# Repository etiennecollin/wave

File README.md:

# Wave <!-- omit from toc -->

 <sub>Wave v0.0.1 + MBK Blank Keycaps</sub>

<span>

</span>

---

- [What Is It](#what-is-it)
- [Features](#features)
- [Components List](#components-list)
  - [Keyboard](#keyboard)
  - [Plates Kit](#plates-kit)
- [Ordering the PCBs](#ordering-the-pcbs)
  - [Keyboard](#keyboard-1)
  - [Plates kit](#plates-kit-1)
    - [Switch Plates](#switch-plates)
    - [Back Plates](#back-plates)
- [QMK Firmware](#qmk-firmware)

## What Is It

The Wave is a small, minimalist, reversible keyboard inspired by the [Ferris](https://github.com/pierrechevalier83/ferris), the [Ferris Sweep](https://github.com/davidphilipbarr/Sweep), the [Swoop](https://github.com/jimmerricks/swoop), the [Sweep36](https://github.com/sadekbaroudi/sweep36), the [Piantor](https://github.com/beekeeb/piantor) and the [Chocofi](https://github.com/pashutk/chocofi) (thank you to the amazing creators of these keyboards). It aims to put together everything I like about these other models and to solve a few issues I found with them.

## Features

- Choc V1 switches
  - The switches can be soldered, or hot swapped using either Mill-Max or Kailh hot swap sockets
- Choc spacing (supports MBK keycaps)
- The same column stagger you loved on the [Ferris Sweep](https://github.com/davidphilipbarr/Sweep)
- 1.5u thumb key support
- Diode-less build
- Reversible PCB
- USB-C
- Mini DIN 4 (S-Video) connector used to connect both halves of the keyboard
  - The issue with TRRS connectors is that [they are not hot swap](https://docs.qmk.fm/#/feature_split_keyboard?id=considerations); disconnecting the cable while the keyboard is powered via usb risks damaging/breaking the controller by shorting the VCC pin to a GND or data pin.
  - The Mini DIN 4 connector solves this issue and is readily available on the market, being the cable used for S-Video.
- Switch plate and back plate available
- No LEDs

## Components List

### Keyboard

Here are the **required** components to build the Wave:

- 2x Keyboard PCBs (PCB manufacturers usually sell them in multiples of 5)
- 2x Elite-C V4 controllers
- 36x Choc V1 switches
- 36x MBK compatible keycaps
- 2x Mini DIN 4 Jack ([MDJ-004-FS](https://www.digikey.ca/en/products/detail/adam-tech/MDJ-004-FS/9832525))
- 1x Mini DIN 4 (S-Video) cable
- 1x USB-C Cable to connect to computer

Here are the **optional** components to build the Wave:

- Hot swap sockets, either:
  - 36x Kailh hot swap sockets for Choc switches
  - 72x Mill-Max hot swap sockets (preferably [3305](https://www.digikey.ca/en/products/detail/mill-max-manufacturing-corp/3305-1-15-15-47-27-10-0/13901953) or [7305](https://www.digikey.ca/en/products/detail/mill-max-manufacturing-corp/7305-0-15-15-47-27-10-0/1765737) sockets as they have a thinner profile)
- 2x reset switches ([B3U-1000P-B](https://www.digikey.ca/en/products/detail/omron-electronics-inc-emc-div/B3U-1000P-B/1811777))
  - The B3U-1000PM, B3U-1000P-B and B3U-1000PM-B variants will work as they have the same footprint.
- 10x Rubber feet/bumpers (I like these [RBS-12BK](https://www.digikey.ca/en/products/detail/essentra-components/RBS-12BK/3814603))

### Plates Kit

- 2x Switch plate PCBs (PCB manufacturers usually sell them in multiples of 5)
  - The switch plates may be used without back plates.
- 2x Back plate PCBs (PCB manufacturers usually sell them in multiples of 5)
  - The back plates **require** switch plates to screw into.
- 5x M2 6mm spacer ([970060244](https://www.digikey.ca/en/products/detail/w%C3%BCrth-elektronik/970060244/9488532))
- 10x M2 3mm screws ([I like these torx screws](https://www.ebay.ca/itm/154354213469?var=454428568064))

## Ordering the PCBs

### Keyboard

<sub>Wave PCB</sub>

To order the keyboard PCB, the following settings are recommended[^1]:

| Detail                  | Value                     |
| ----------------------- | ------------------------- |
| Gerber file             | `Wave_0.0.1.zip`          |
| Base material           | FR-4                      |
| Layers                  | 2                         |
| Different design        | 1                         |
| Delivery format         | Single PCB                |
| PCB thickness           | **1.6mm**                 |
| PCB color               | (Personal preference)     |
| Silkscreen              | (Personal preference)     |
| Surface finish          | (Personal preference)[^2] |
| Outer copper weight     | 1oz                       |
| Via Covering            | Tented                    |
| Board Outline Tolerance | ±0.2mm(Regular)           |
| Confirm production file | No                        |
| Remove order number     | Yes                       |
| Gold Fingers            | No                        |
| Castellated holes       | No                        |

### Plates kit

You will need to order two different PCBs; the switch plate one and the back plate one.

#### Switch Plates

<sub>Wave Switch Plate PCB</sub>

 <sub>Wave v0.0.1 Switch Plate</sub>

To order the switch plate PCB, the following settings are recommended[^1]:

| Detail                  | Value                         |
| ----------------------- | ----------------------------- |
| Gerber file             | `Wave_Switch_Plate_0.0.1.zip` |
| Base material           | FR-4                          |
| Different design        | 1                             |
| Layers                  | 2                             |
| Delivery format         | Single PCB                    |
| PCB thickness           | **1.2mm**                     |
| PCB color               | (Personal preference)         |
| Silkscreen              | (Personal preference)         |
| Surface finish          | (Personal preference)[^2]     |
| Outer copper weight     | 1oz                           |
| Via Covering            | Tented                        |
| Board Outline Tolerance | ±0.2mm(Regular)               |
| Confirm production file | No                            |
| Remove order number     | Yes                           |
| Gold Fingers            | No                            |
| Castellated holes       | No                            |

#### Back Plates

<sub>Wave Back Plate PCB</sub>

 <sub>Wave v0.0.1 Back Plate</sub>

To order the back plate PCB, the following settings are recommended[^1]:

| Detail                  | Value                       |
| ----------------------- | --------------------------- |
| Gerber file             | `Wave_Back_Plate_0.0.1.zip` |
| Base material           | FR-4                        |
| Different design        | 1                           |
| Layers                  | 2                           |
| Delivery format         | Single PCB                  |
| PCB thickness           | **1.6mm**                   |
| PCB color               | (Personal preference)       |
| Silkscreen              | (Personal preference)       |
| Surface finish          | (Personal preference)[^2]   |
| Outer copper weight     | 1oz                         |
| Via Covering            | Tented                      |
| Board Outline Tolerance | ±0.2mm(Regular)             |
| Confirm production file | No                          |
| Remove order number     | Yes                         |
| Gold Fingers            | No                          |
| Castellated holes       | No                          |

## QMK Firmware

The [latest firmware](https://github.com/qmk/qmk_firmware/tree/master/keyboards/etiennecollin/wave) can be found on the official [QMK](https://github.com/qmk/qmk_firmware/tree/master) repository.

[^1]: Settings are for [JLCPCB](https://jlcpcb.com/), but should be similar with other manufacturers.
[^2]: ROHS or lead-free options should be preferred (LeadFree HASL).

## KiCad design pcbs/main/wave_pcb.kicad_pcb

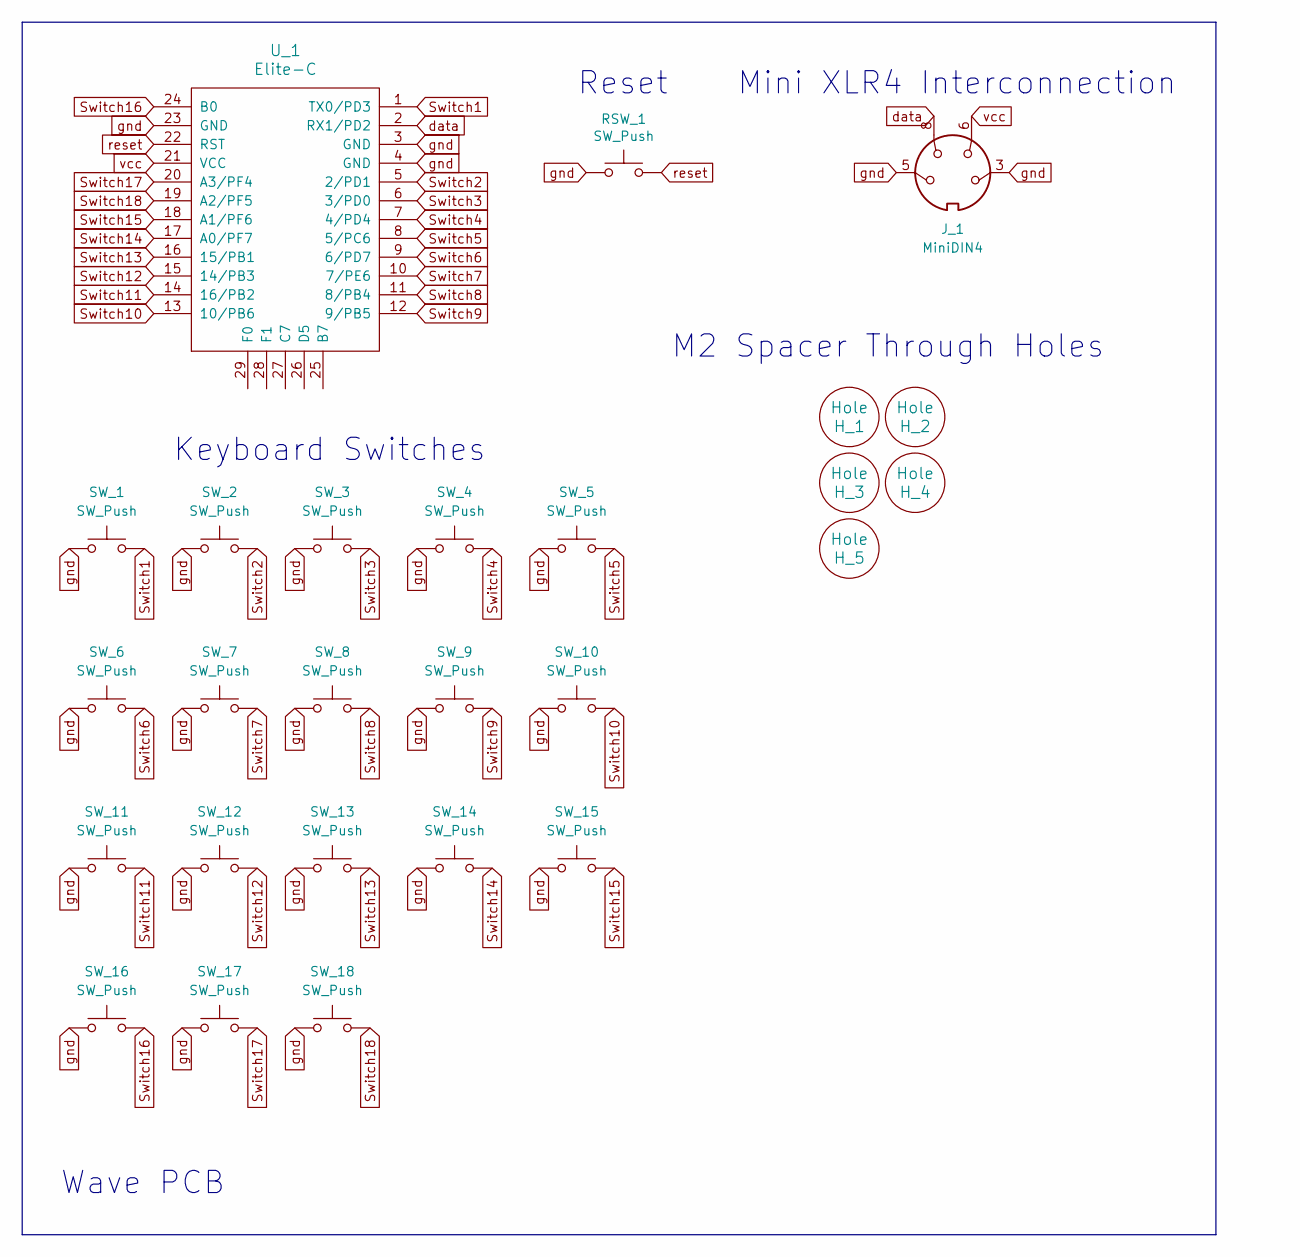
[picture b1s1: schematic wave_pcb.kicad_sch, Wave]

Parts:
H_1, H_2, H_3, H_4, H_5: Hole; Würth_Elektronik_970060244_M2_spacer_hole_pad
J_1: MiniDIN4; AdamTech_MDJ-004-FS_reversible
RSW_1: SW_Push; Omron_B3U-1000P-B_reversible
SW_1, SW_2, SW_3, SW_4, SW_5, SW_6, SW_7, SW_8, SW_9, SW_10, SW_11, SW_12, SW_13, SW_14, SW_15, SW_17, SW_18: SW_Push; Kailh_socket_PG1350_1.00u_optional_millmax_reversible
SW_16: SW_Push; Kailh_socket_PG1350_1.50u_optional_millmax_reversible
U_1: Elite-C; Elite-C-upsideDown_reversible

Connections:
Switch1: SW_1.1, U_1.1 (TX0/PD3)
Switch2: SW_2.1, U_1.5 (2/PD1)
Switch3: SW_3.1, U_1.6 (3/PD0)
Switch4: SW_4.1, U_1.7 (4/PD4)
Switch5: SW_5.1, U_1.8 (5/PC6)
Switch6: SW_6.1, U_1.9 (6/PD7)
Switch7: SW_7.1, U_1.10 (7/PE6)
Switch8: SW_8.1, U_1.11 (8/PB4)
Switch9: SW_9.1, U_1.12 (9/PB5)
Switch10: SW_10.1, U_1.13 (10/PB6)
Switch11: SW_11.1, U_1.14 (16/PB2)
Switch12: SW_12.1, U_1.15 (14/PB3)
Switch13: SW_13.1, U_1.16 (15/PB1)
Switch14: SW_14.1, U_1.17 (A0/PF7)
Switch15: SW_15.1, U_1.18 (A1/PF6)
Switch16: SW_16.1, U_1.24 (B0)
Switch17: SW_17.1, U_1.20 (A3/PF4)
Switch18: SW_18.1, U_1.19 (A2/PF5)
data: J_1.8, U_1.2 (RX1/PD2)
gnd: J_1.3, J_1.5, RSW_1.1, SW_1.2, SW_2.2, SW_3.2, SW_4.2, SW_5.2, SW_6.2, SW_7.2, SW_8.2, SW_9.2, SW_10.2, SW_11.2, SW_12.2, SW_13.2, SW_14.2, SW_15.2, SW_16.2, SW_17.2, SW_18.2, U_1.3 (GND), U_1.4 (GND), U_1.23 (GND)
reset: RSW_1.2, U_1.22 (RST)
vcc: J_1.6, U_1.21 (VCC)

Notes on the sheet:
Keyboard Switches
Mini XLR4 Interconnection
M2 Spacer Through Holes
Wave PCB
Reset

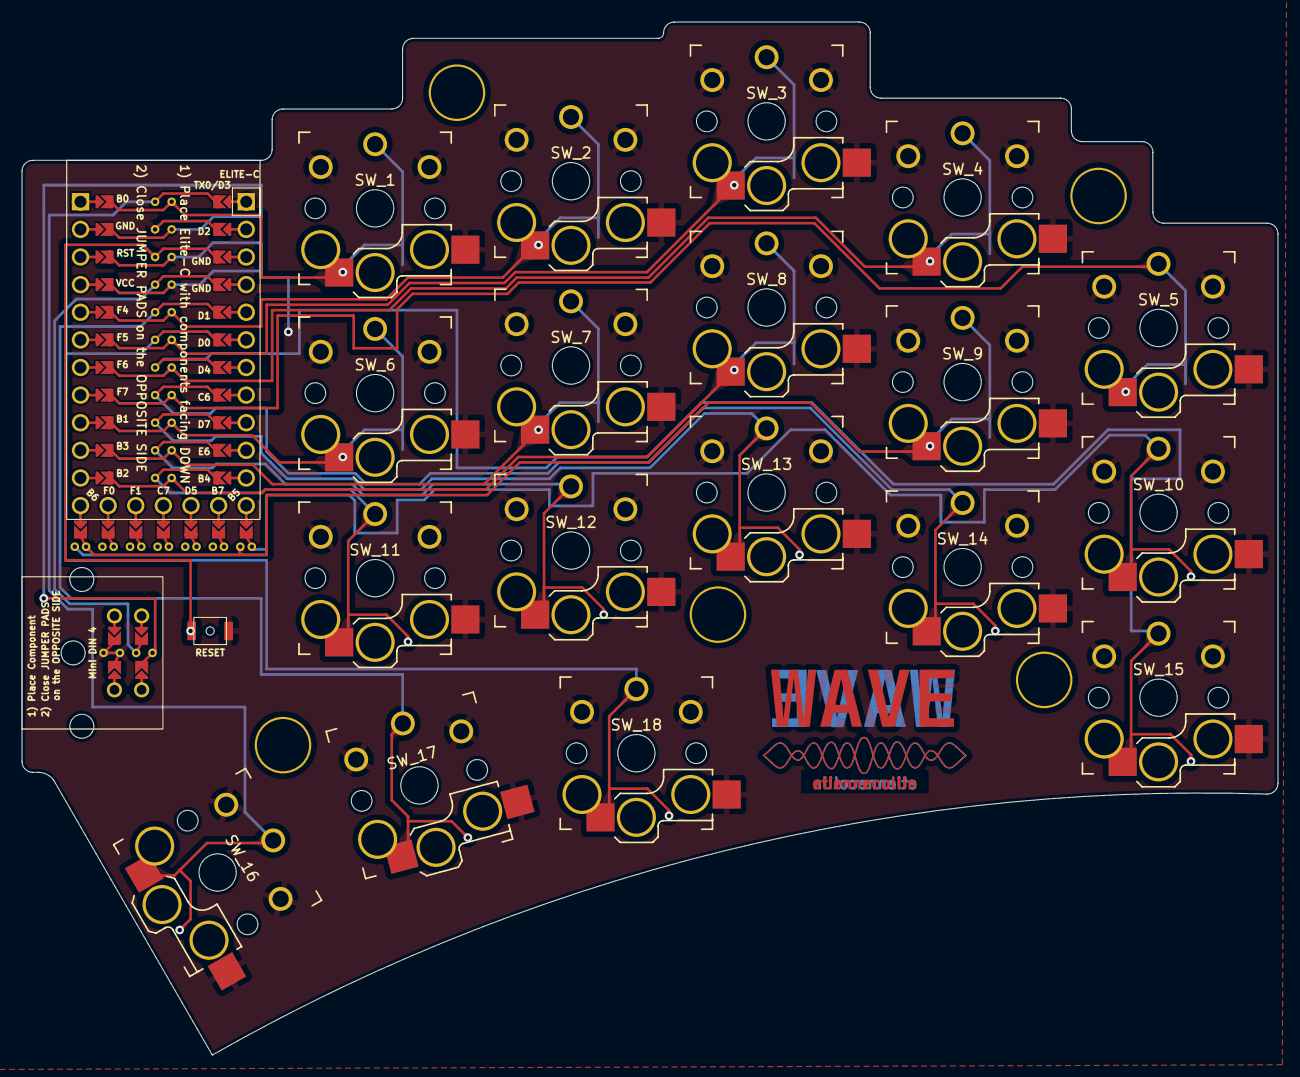
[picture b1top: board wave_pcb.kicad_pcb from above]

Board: 2 copper layers, 115.5 x 95.0 mm, 28 parts (0 on the bottom side), 22 nets.

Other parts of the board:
LOGO***: logo_wave_back; logo_wave
name: logo_username

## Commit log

2023-09-07 Created logos
2023-09-07 Created main PCB
2023-09-07 Created back plate
2023-09-07 Created switch plate
2023-09-07 Created README.md
2023-09-07 Added PCB renders
2023-09-07 Updated capitalization
2023-09-07 Update issue templates
2023-09-11 Fixed spacing of PCB edges
2023-09-12 Added link to icons
2023-09-12 Specified Mini DIN 4 cable use
2023-09-12 Added links to Mill Max sockets
2023-09-12 Updated PCB renders
2023-10-10 Moved files
2023-10-10 Firmware now available
    - Added QMK icons
2023-10-12 Added build images
2023-10-12 Updated parts list
2023-10-12 Updated description
2024-04-03 Formatting

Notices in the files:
README.md:
https://img.shields.io/static/v1?label=license&message=GPL-3.0&color=success
